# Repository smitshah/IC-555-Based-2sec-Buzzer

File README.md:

# IC-555-Based-2sec-Buzzer

**Problem statement:**

Design a circuit using IC 555 that will switch the buzzer ON for 2sec after giving a trigger pulse only.

**INTRODUCTION:**

The objective of this project is to familiarize ourselves with the various applications of Schmitt Trigger using IC 555 and to recognize their use in real life conditions. Our topic was to create a circuit which would turn the Buzzer on only when a trigger pulse is applied. These circuits can be used in real life applications like buzzer alarms, doorbells, buzzers during quizzes, timers etc. Our buzzer is meant to buzz only for 2 seconds after an interval of two seconds. Hence, we used resistors of value such that our Ton and Toff would come to be approximately 2 seconds each. This project’s aim is to help us in brushing up our skills of recreating a given circuit on two software’s, KiCAD and LTSpice. It is also meant to construct the circuit on the breadboard and PCB after the process of etching.

**MATERIALS USED:**
* NE555
* 220kΩ Resistor
* 100kΩ Resistor
* 10µF Capacitors
* Buzzers 
* Connecting wires
* Power supply
* Breadboard
* Copper Clad

**CHOOSING THE CORRECT CIRCUIT DIAGRAM:**

Our first step for this project was to find the most appropriate and efficient circuit diagram that would help us achieve the required output. After a lot of consultation from textbooks and online websites, we chose a circuit diagram that was best for our application. 

We recreated the circuit diagram on LTspice, a software that allows us to replicate the circuit diagram with the appropriate components connected to it, to run the simulation and achieve and actual output of the circuit. Using the software, we observed the output for various values of resistors and capacitors. Resistor R1 is responsible for Ton value and R2 is responsible for Toff value. After a lot of trial and error, we got our require values of R1, R2, C1 and C2 for the needed Ton and Toff values of 2 seconds. R1 came out to be 100K ohm, R2 came out to be 220K ohm and C1 and C2 both came out to be 10uF. As this circuit keeps switching from ON to OFF, it is called an Astable Multivibrator circuit, using IC555. 

The LTspice circuit diagram and output of the software is as shown:

Circuit Diagram:

Output *(Ton and Toff is approximately 2 seconds each)*:

**BREADBOARD MOUNTING:**

Following the circuit diagram chosen, we get the appropriate components and place them on the breadboard. Breadboard connections are temporary connects and help us to identify if our circuit is actually working or giving us the required output with the live working components in place. It also helps us to certain if the components are in correct working order or no.

**KiCAD SCHEMATIC:**

After the testing of the circuit using the breadboard, we move onto the next software, KiCAD. Using KiCAD we can lay the foundation of our final PCB circuit. We start off with a rough schematic of our circuit which will closely resemble the circuit that we had produced on LTspice. The schematic gives us a general idea of what the circuit may comprise of and how many components are used. After this, we move onto footprint allocation, which is the process where the software identifies which exact components we are using and their respective dimensions so that the process of soldering may take place properly without any issues with the size of the components or so. 

The schematic and footprint allocation for our circuit is as below:

KiCAD Schematic:

Footprint Allocation to the Schematic:

**KiCAD GERBER FILE GENERATION:**

After footprint allocation, we move to net-list generation which is the process of importing the footprint allocation onto a virtual PCB. Here, we can place the components in the most effective manner onto our PCB board and can hence visualise how our final PCB structure look like by viewing the virtual 3D model. We can then complete the tracking and override them to make it most effective. We can choose the layers of the PCB we need in our final output and create a gerber file of it. We can save the gerber file in PDF format also. This PDF file is collection of all the layers of the PCB that we choose to have. Out of all of these files, the most important one is B.Cu file. It is the back copper tracking between all these components of our final PCB.

Final PCB Layout:

The 3-D view of front-side and back-side our PCB is as below:

**TONER TRANSFER:**

Toner transfer is the process by which we create our actual track of our circuit. We take the B.Cu file (PDF Format) and get it printed on a photo paper with a good quality ink. After the printout is taken, it is placed upside down on the copper clad and is taped down to it. We then cover it with a piece of cloth and heat it with the help of Iron. We press it down and run the iron over it until the ink is transferred onto the copper clad from the paper. This process of transferring ink from photo paper onto copper clad is called toner transfer.

**ETCHING:**

Etching is a method used for the production of the PCBs where acid is used to remove unwanted copper from a prefabricated laminate. This is done by applying a temporary mask (in our case, ink), that protects part of the laminate from the acid and leaves the desired copper layer untouched. The etching solution used by us is ferric chloride. Thus, we dip the PCB in boiling FeCl3 solution and wait until the excess copper is dissolved off and only our tracks of circuit remains. After this is done, we take out the board and clean it using water.

**DRILLING AND SOLDERING:**

After cleaning the board, we proceed to drill the board using a PCB drilling machine. We make holes of diameter approximately 1mm. Holes are made wherever components have to be placed. After all the holes are drilled, we proceed to place the components in their respective slots following the PCB layout. Once the components are placed, we solder them so that they stay in place and the connections are complete. We also solder other wires where external connections are required. After soldering, we clean our PCB with IP(Iso-propyl Alcohol) so that the residue of solder is removed. Now our circuit is ready to use. 

Now, we provide the trigger pulse to the input terminal of our circuit and check the operation of the buzzer. If all the above process are carried out in the correct manner, then our buzzer should buzz with the appropriate time intervals.

Actual PCB *(Circuit on Copper Clad)*:

**CONCLUSION:**

Hence, through this project we saw how to create a buzzer circuit using IC 555 and saw all the processes required to achieve our final circuit. This project helped us in brushing up our skills for PCB designing which may be of great use for us in the future. These skills help us develop working circuits right from scratch until the very end. Hence, we can come up with circuits wherever we are, by just learning these few steps.

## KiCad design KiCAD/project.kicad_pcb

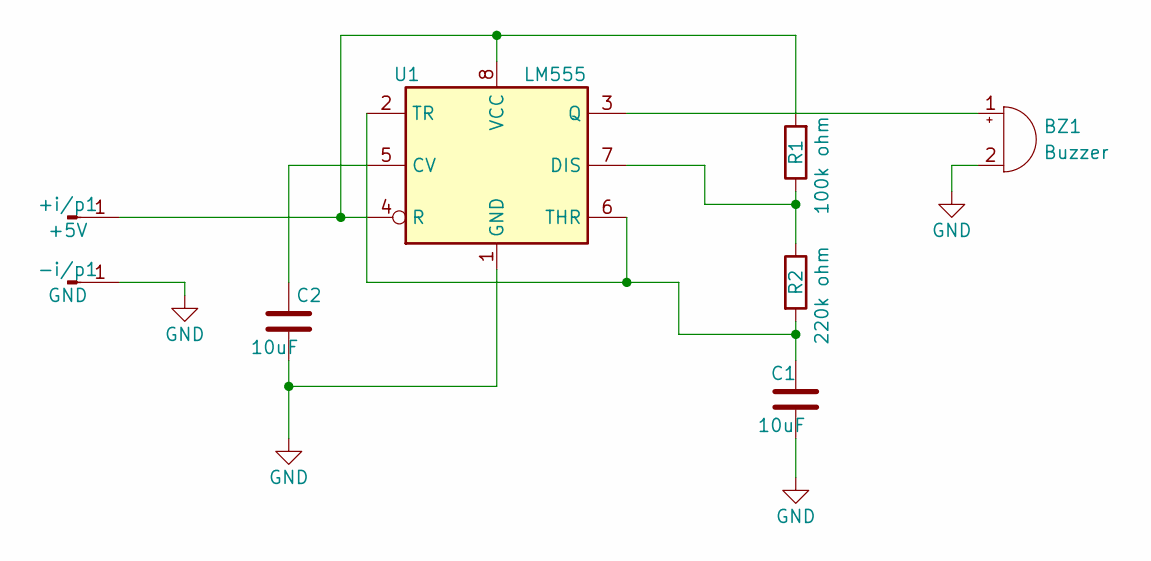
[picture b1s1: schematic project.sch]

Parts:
+i/p1: +5V; Pin_Header_Angled_1x01_Pitch1.27mm
-i/p1: GND; Pin_Header_Angled_1x01_Pitch1.27mm
BZ1: Buzzer; Buzzer_12x9.5RM7.6
C1, C2: 10uF; C_Disc_D4.3mm_W1.9mm_P5.00mm
R1: 100k ohm; R_Axial_DIN0309_L9.0mm_D3.2mm_P15.24mm_Horizontal
R2: 220k ohm; R_Axial_DIN0309_L9.0mm_D3.2mm_P15.24mm_Horizontal
U1: LM555; DIP-8_W7.62mm_Socket

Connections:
GND: -i/p1.1, BZ1.2 (+), C1.2, C2.2, U1.1 (GND)
unnamed: +i/p1.1, R1.2, U1.4 (R), U1.8 (VCC)
unnamed: BZ1.1 (-), U1.3 (Q)
unnamed: C1.1, R2.2, U1.2 (TR), U1.6 (THR)
unnamed: C2.1, U1.5 (CV)
unnamed: R1.1, R2.1, U1.7 (DIS)

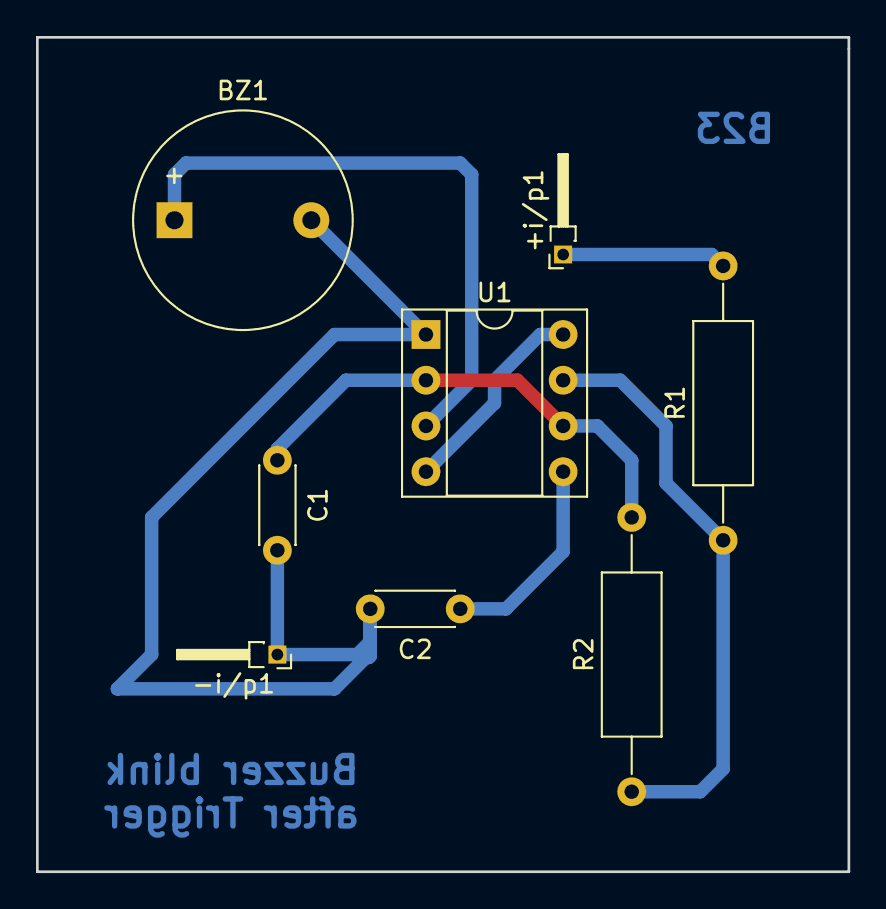
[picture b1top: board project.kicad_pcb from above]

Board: 2 copper layers, 45.1 x 46.4 mm, 8 parts (0 on the bottom side), 6 nets.
